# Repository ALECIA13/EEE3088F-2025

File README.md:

# EEE3088F-2025 Micro-Mouse Power Module

**Authors:** Khanyisa Hlungwani & Maitele Makungo

## Project Description

This repository contains the **Power Module** for a Micro-Mouse robot project, developed as part of the EEE3088F (2025) course. The Micromouse is a small autonomous robot designed to navigate and solve a maze, consisting of various subsystems (sensors, motors, control, and power). The Power Module handles all aspects of power distribution and management for the robot, ensuring that each component receives stable and sufficient power. It includes the circuitry for the robot’s battery power supply, voltage regulation for logic and sensors, and motor driver outputs, along with safety features like battery monitoring and charging control. Overall, this module is crucial for delivering reliable power to the Micro-Mouse, allowing it to operate safely and efficiently during maze-solving runs.

## Scope and Responsibilities

The design and implementation of the Power Module were divided between two team members, each focusing on specific functional areas:

* **Khanyisa Hlungwani:** Responsible for the **motor control** circuitry and **battery management**. This includes the motor driver hardware for the drive motors, the **battery monitoring** system to track battery voltage/health, and the **battery charging** circuit to safely recharge the robot’s Li-ion/Li-Po battery pack. Khanyisa’s design ensures the motors receive the appropriate power and that the battery is used and charged safely (with over-voltage and over-discharge protection as needed).

* **Maitele Makungo:** Responsible for the **power input interface** and **voltage regulation**. This includes the **USB-C interface** for external power/charging (allowing the robot to be powered or charged via a USB-C source), the design of **voltage regulators** (to step down or regulate battery/USB voltage to the required levels for various components such as 5V, 3.3V, etc.), and overall **power management** circuitry. Maitele’s design ensures stable regulated voltages for all electronics and handles power switching logic (for example, switching between USB power and battery, and implementing any necessary protection like current limiting or short-circuit protection).

By splitting the responsibilities, each student focused on their section of the power system while ensuring that the two parts integrate seamlessly into a single Power Module that meets the Micro-Mouse’s requirements.

## Repository Contents

The repository is organized into folders and files that represent different aspects of the Power Module design:

* **Schematics** – Contains the electrical schematics of the power module. This includes complete circuit diagrams for the battery charger/monitor, motor driver circuits, USB-C power input circuitry, and voltage regulators. The schematics are provided in the chosen EDA tool format (and may include PDF exports for easy viewing). **(e.g.,** files like `PowerModule_Schematic.pdf` and the source schematic design files **)**

* **PCB Layout** – Contains the PCB design files and layout information for the power module’s printed circuit board. This includes the board layout file from the PCB design software, as well as generated manufacturing files (Gerber files, drill files) and possibly images of the PCB layout. **(e.g.,** a board file `PowerModule_PCB.kicad_pcb` or Altium project, and exported images like `PCB_Top.png`, `PCB_Bottom.png` **)**

* **Final Design** – This folder includes the finalized documentation and outputs of the project. It typically contains the final report or design document for the power module, a Bill of Materials (BOM) listing all components used, and any presentation slides or additional references. It may also include **final revision** schematic/PCB printouts and assembly drawings, as well as test results or data from the completed module. In short, the **Final Design** folder serves as a comprehensive package of the finished power module design and can be used for review or submission purposes.

## Usage and Integration

The Power Module is designed to integrate with the Micro-Mouse robot’s overall system (often via a main control board or motherboard). Key connections and usage notes include:

* **Power Input:** The module can be powered via the on-board battery or through the USB-C port. When the Micro-Mouse is operating untethered, it draws power from the battery. When plugged into USB-C, the system can charge the battery and/or run the robot from USB power (with proper regulation and without overcharging the battery).

* **Outputs to Other Modules:** The Power Module provides regulated output lines (e.g., 5V, 3.3V) that connect to the Micro-Mouse’s other subsystems (like the sensor module and control electronics) via a designated connector. It also provides the motor driver outputs that connect directly to the motors on the chassis. These interface connections are clearly labeled in the schematic and on the PCB silkscreen for easy assembly.

* **Battery Monitoring:** The on-board battery voltage sensor can be read by the main controller (or a dedicated microcontroller on the power board) to determine the battery charge level. This allows the robot’s software to warn about low battery or manage charging states. Users should ensure the battery is within safe voltage ranges during operation (the module includes under-voltage lockout to protect the battery).

* **Charging:** To charge the robot, connect a USB-C cable to the Power Module’s port. The charging circuit will automatically manage the charging current and cutoff based on the battery’s state. Indicator LEDs (if included on the PCB) may show the charging status (charging, full, etc.). It’s recommended to refer to the **Final Design** document for specifics on the charging procedure and any jumpers or switches related to power sourcing.

## Getting Started

To get started with this Power Module repository:

1. **Clone the Repository:** Download or clone the repo to access all design files. Ensure you have the necessary software to open the schematic (`Schematics` folder) and PCB layout files (`PCB Layout` folder). For example, if the design was done in KiCad, download KiCad to open the project; if Altium, use Altium Designer, etc.

2. **Open the Schematic:** Review the power module schematic to understand the circuit design. This can be found in the **Schematics** folder (use the PDF for a quick view, or the source file for editing). The schematic is annotated with comments to explain the role of each section (battery charger, motor driver, etc.).

3. **Examine the PCB Layout:** Open the PCB design in the appropriate software to see component placement and routing. Alternatively, view the provided PCB images in the **PCB Layout** folder to get an overview of the board’s design (component locations, board dimensions, connectors, etc.).

4. **Read the Documentation:** In the **Final Design** folder, read the final report or documentation which includes detailed descriptions of design decisions, testing procedures, and results. This will provide insight into why certain components were chosen and how the module was verified to meet requirements.

5. **Integration:** If you are integrating this Power Module with your own Micro-Mouse project, use the interfacing information (pinouts and diagrams) provided in the documentation to connect the module properly. The **Micro-Mouse System Interfacing** section of the report (in **Final Design**) describes how this power board connects to the main controller board and motors.

## Contributing

This project was completed as an academic course project by the authors, so it may not be open for external contributions in the usual sense. However, if you are an instructor or student looking to use this design as a reference or extend it:

* Feel free to fork the repository for your own educational use.
* If you find issues or have suggestions, you can contact the authors or open an issue for discussion.
* Ensure to credit the original authors (Khanyisa Hlungwani and Maitele Makungo) if you derive or use significant portions of this design in your own project.

## Acknowledgments

* **Course Instructors and Mentors:** Thank you to the EEE3088F course instructors for guidance throughout the project, and for providing the framework and resources for the Micro-Mouse competition project.
* **Teammates:** Appreciation to each other as team members for the collaboration and division of work that made this Power Module successful.
* **Resources:** The Micro-Mouse community and prior projects provided inspiration and insight. Resources like online Micromouse forums and documentation helped shape the design (for example, understanding common voltage requirements and battery choices for micromouse robots).

---

*This README provides an overview of the Power Module for the EEE3088F-2025 Micro-Mouse project. For detailed schematics, PCB layouts, and test results, please refer to the files and documentation within this repository. We hope this information is helpful for anyone studying or building a Micro-Mouse power system.*

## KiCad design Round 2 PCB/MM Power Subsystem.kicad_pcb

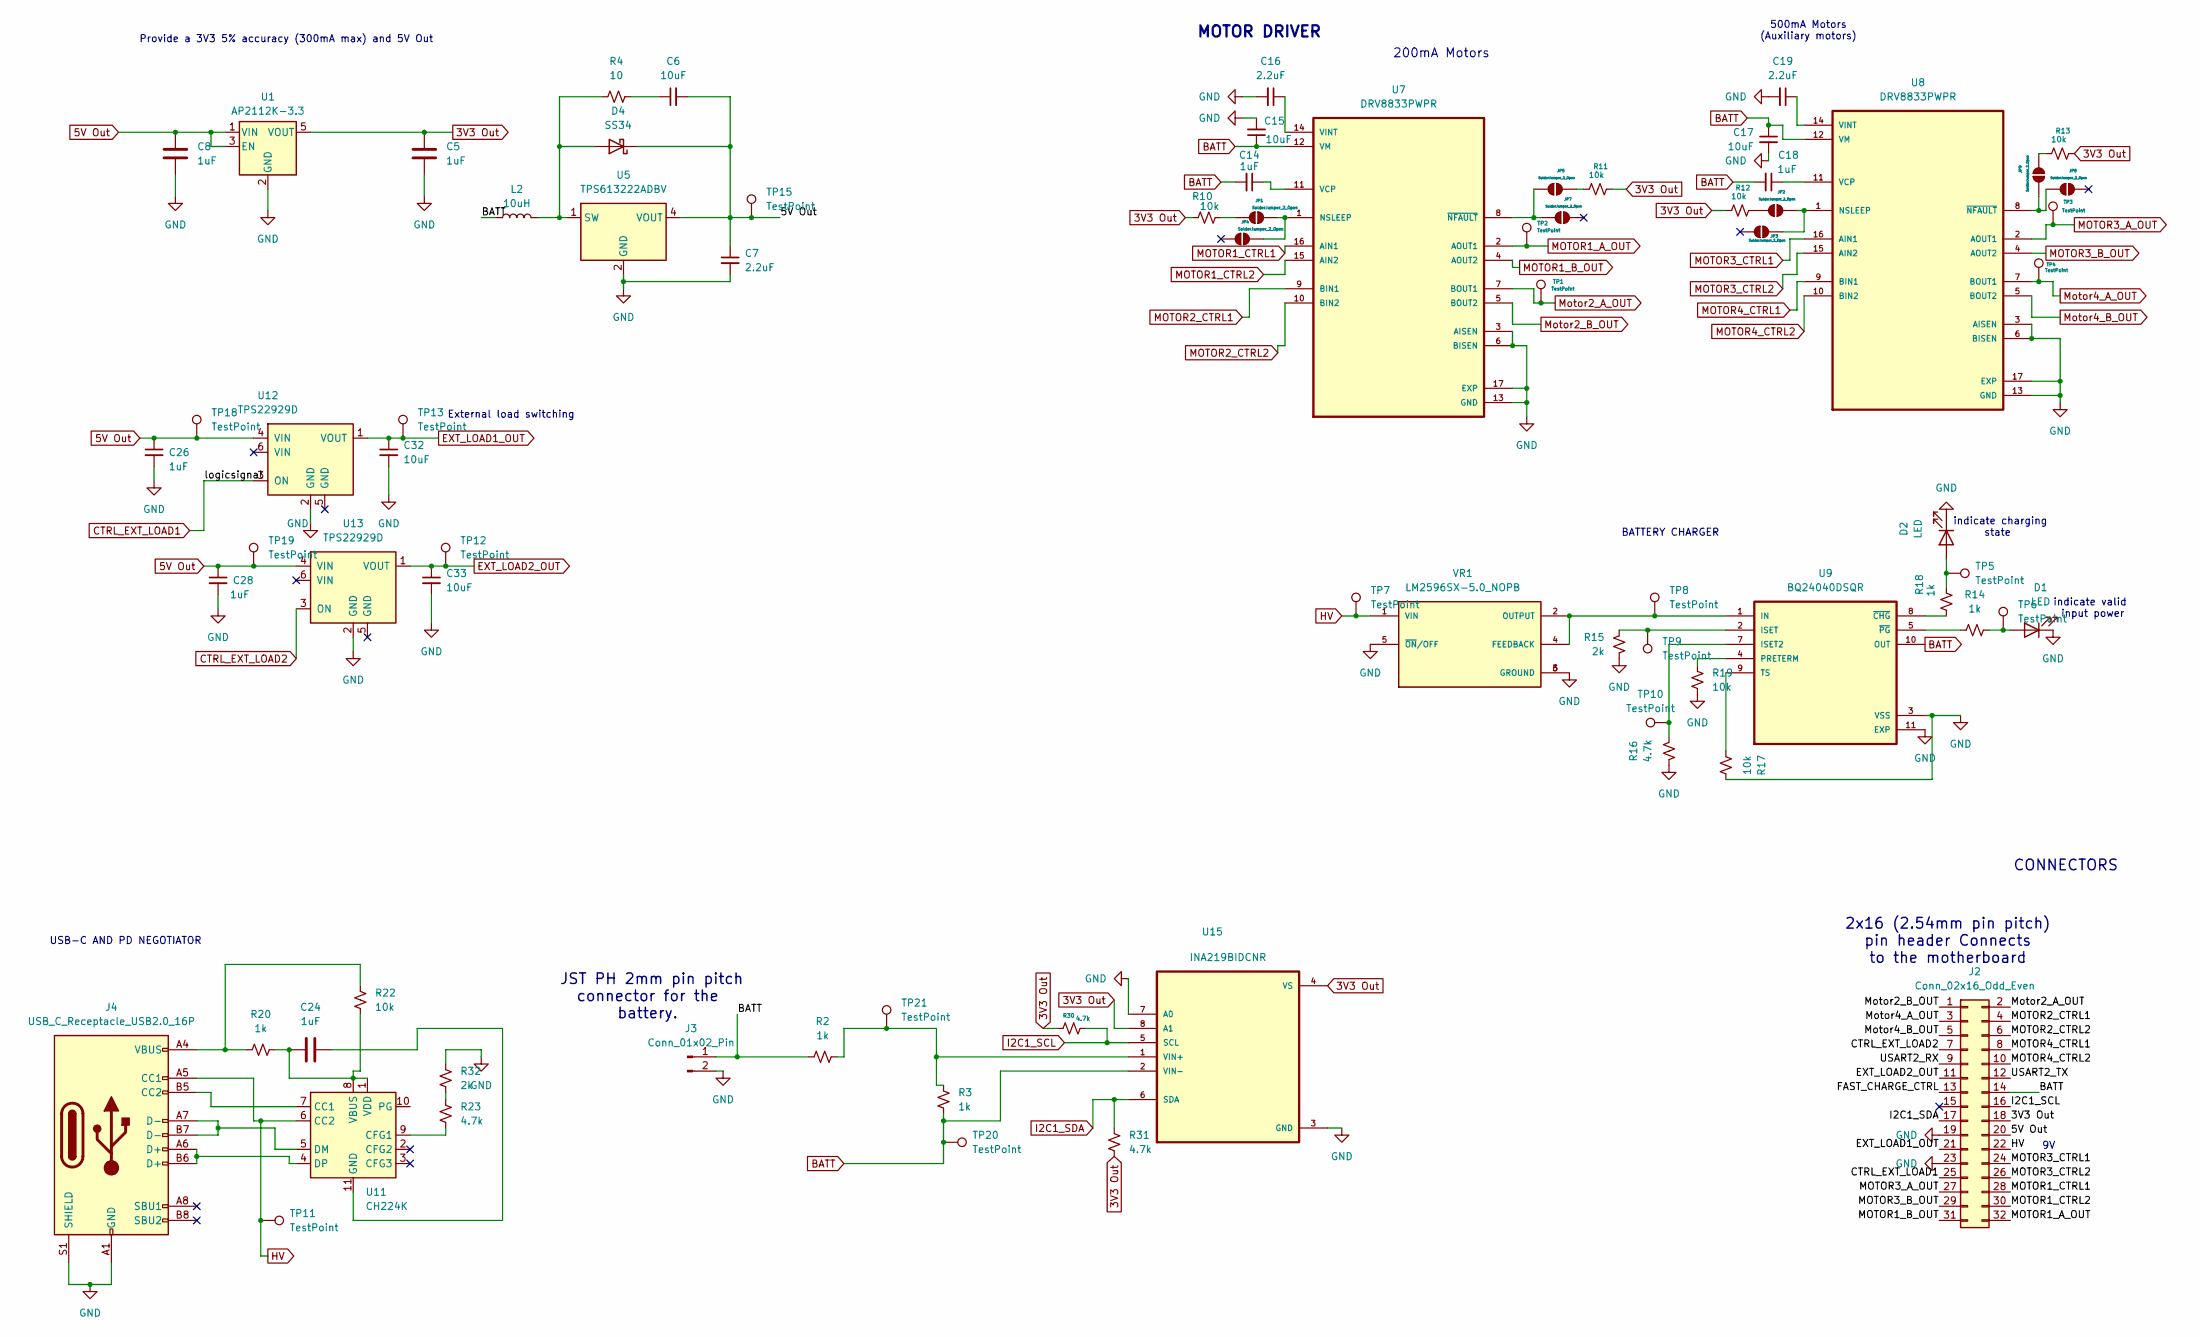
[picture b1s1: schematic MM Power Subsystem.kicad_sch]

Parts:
C5, C8, C14, C18, C24, C26, C28: 1uF; C_0402_1005Metric_Pad0.74x0.62mm_HandSolder
C6, C15, C17, C32, C33: 10uF; C_0402_1005Metric_Pad0.74x0.62mm_HandSolder
C7, C16, C19: 2.2uF; C_0402_1005Metric_Pad0.74x0.62mm_HandSolder
D1, D2: LED; LED_0805_2012Metric_Pad1.15x1.40mm_HandSolder
D4: SS34; D_SMA
J2: Conn_02x16_Odd_Even; PinHeader_2x16_P2.54mm_Vertical
J3: Conn_01x02_Pin; JST_PH_S2B-PH-K_1x02_P2.00mm_Horizontal
J4: USB_C_Receptacle_USB2.0_16P; USB_C_Receptacle_HCTL_HC-TYPE-C-16P-01A; LCSC C134092
JP1, JP2, JP3, JP4, JP5, JP7, JP8, JP9: SolderJumper_2_Open; SolderJumper-2_P1.3mm_Open_RoundedPad1.0x1.5mm
L2: 10uH; L_0201_0603Metric_Pad0.64x0.40mm_HandSolder
R2, R3, R14, R18, R20: 1k; R_0402_1005Metric_Pad0.72x0.64mm_HandSolder
R4: 10; R_0402_1005Metric_Pad0.72x0.64mm_HandSolder
R10, R11, R12, R13, R17, R19, R22: 10k; R_0402_1005Metric_Pad0.72x0.64mm_HandSolder
R15, R32: 2k; R_0402_1005Metric_Pad0.72x0.64mm_HandSolder
R16, R23, R30, R31: 4.7k; R_0402_1005Metric_Pad0.72x0.64mm_HandSolder
TP1, TP2, TP3, TP4, TP5, TP6, TP7, TP8, TP9, TP10, TP11, TP12, TP13, TP15, TP18, TP19, TP20, TP21: TestPoint; TestPoint_Pad_D2.0mm
U1: AP2112K-3.3; SOT-23-5
U5: TPS613222ADBV; SOT-23-5; LCSC C2071163
U7, U8: DRV8833PWPR; TSSOP-16-1EP_4.4x5mm_P0.65mm_EP3x3mm; PARTREV E; LCSC C50506
U9: BQ24040DSQR; WSON-10-1EP_2.5x2.5mm_P0.5mm_EP1.2x2mm; LCSC C81080
U11: CH224K; SSOP-10-1EP_3.9x4.9mm_P1mm_EP2.1x3.3mm
U12, U13: TPS22929D; SOT-23-6; LCSC C415177
U15: INA219BIDCNR; SOT65P280X145-8N
VR1: LM2596SX-5.0_NOPB; VREG_LM2596SX-5.0_NOPB; PARTREV F; LCSC C10002

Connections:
3V3 Out: C5.1, J2.18, R10.2, R11.1, R12.2, R13.1, R30.2, R31.2, U1.5 (VOUT), U15.4 (VS), U15.8 (A1)
5V Out: C6.2, C7.1, C8.1, C26.1, C28.1, D4.1 (K), J2.20, TP15.1, TP18.1, TP19.1, U1.1 (VIN), U1.3 (EN), U5.4 (VOUT), U12.4 (VIN), U13.4 (VIN)
/FAST_CHARGE_CTRL: J2.13
/MOTOR1_A_OUT: J2.32
/MOTOR1_CTRL1: J2.28
/MOTOR1_CTRL2: J2.30
/MOTOR2_CTRL1: J2.4
/MOTOR2_CTRL2: J2.6
/MOTOR3_A_OUT: J2.27
/MOTOR3_B_OUT: J2.29
/MOTOR3_CTRL1: J2.24
/MOTOR4_CTRL1: J2.8
/Motor2_B_OUT: J2.1
/Motor4_B_OUT: J2.5
/USART2_RX: J2.9
/USART2_TX: J2.12
BATT: C14.2, C15.1, C17.1, C18.2, J2.14, J3.1, L2.1, R2.2, R3.2, TP20.1, U7.12 (VM), U8.12 (VM), U9.10 (OUT), U15.2 (VIN-)
CTRL_EXT_LOAD1: J2.25, U12.3 (ON)
CTRL_EXT_LOAD2: J2.7, U13.3 (ON)
EXT_LOAD1_OUT: C32.1, J2.21, TP13.1, U12.1 (VOUT)
EXT_LOAD2_OUT: C33.1, J2.11, TP12.1, U13.1 (VOUT)
GND: C5.2, C7.2, C8.2, C15.2, C16.2, C17.2, C19.2, C26.2, C28.2, C32.2, C33.2, D1.1 (K), D2.1 (K), J2.19, J2.23, J3.2, J4.A1 (GND), J4.A12 (GND), J4.B1 (GND), J4.B12 (GND), J4.S1 (SHIELD), R15.1, R16.1, R17.1, R19.2, R32.1, U1.2 (GND), U5.2 (GND), U7.3 (AISEN), U7.6 (BISEN), U7.13 (GND), U7.17 (EXP), U8.3 (AISEN), U8.6 (BISEN), U8.13 (GND), U8.17 (EXP), U9.3 (VSS), U9.11 (EXP), U12.2 (GND), U13.2 (GND), U15.3 (GND), U15.7 (A0), VR1.3 (GROUND), VR1.5 (~ON/OFF), VR1.6 (GROUND)
HV: J2.22, J4.A5 (CC1), TP7.1, TP11.1, U11.6 (CC2), VR1.1 (VIN)
I2C1_SCL: J2.16, R30.1, U15.5 (SCL)
I2C1_SDA: J2.17, R31.1, U15.6 (SDA)
MOTOR1_A_OUT: TP2.1, U7.2 (AOUT1)
MOTOR1_B_OUT: J2.31, U7.4 (AOUT2)
MOTOR1_CTRL1: U7.16 (AIN1)
MOTOR1_CTRL2: U7.15 (AIN2)
MOTOR2_CTRL1: U7.9 (BIN1)
MOTOR2_CTRL2: U7.10 (BIN2)
MOTOR3_A_OUT: TP3.1, U8.2 (AOUT1)
MOTOR3_B_OUT: U8.4 (AOUT2)
MOTOR3_CTRL1: U8.16 (AIN1)
MOTOR3_CTRL2: J2.26, U8.15 (AIN2)
MOTOR4_CTRL1: U8.9 (BIN1)
MOTOR4_CTRL2: J2.10, U8.10 (BIN2)
Motor2_A_OUT: J2.2, TP1.1, U7.7 (BOUT1)
Motor2_B_OUT: U7.5 (BOUT2)
Motor4_A_OUT: J2.3, TP4.1, U8.7 (BOUT1)
Motor4_B_OUT: U8.5 (BOUT2)
unnamed: C6.1, R4.1
unnamed: D1.2 (A), R14.1, TP6.1
unnamed: D2.2 (A), R18.1, TP5.1
unnamed: D4.2 (A), L2.2, R4.2, U5.1 (SW)
unnamed: J4.B5 (CC2), U11.7 (CC1)
unnamed: J4.A4 (VBUS), J4.A9 (VBUS), J4.B4 (VBUS), J4.B9 (VBUS), R20.1, R22.1
unnamed: JP1.1 (A), R10.1
unnamed: JP1.2 (B), JP4.2 (B), U7.1 (NSLEEP)
unnamed: JP2.1 (A), R12.1
unnamed: JP2.2 (B), JP3.2 (B), U8.1 (NSLEEP)
unnamed: JP5.1 (A), JP7.1 (A), U7.8 (~NFAULT)
unnamed: JP5.2 (B), R11.2
unnamed: JP8.1 (A), JP9.1 (A), U8.8 (~NFAULT)
unnamed: JP9.2 (B), R13.2
unnamed: R23.1, R32.2
unnamed: C14.1, U7.11 (VCP)
unnamed: C16.1, U7.14 (VINT)
unnamed: C18.1, U8.11 (VCP)
unnamed: C19.1, U8.14 (VINT)
unnamed: TP8.1, U9.1 (IN), VR1.2 (OUTPUT), VR1.4 (FEEDBACK)
unnamed: R16.2, TP10.1, U9.7 (ISET2)
unnamed: R15.2, TP9.1, U9.2 (ISET)
unnamed: R19.1, U9.4 (PRETERM)
unnamed: R17.2, U9.9 (TS)
unnamed: R18.2, U9.8 (~CHG)
unnamed: R14.2, U9.5 (~PG)
unnamed: R23.2, U11.9 (CFG1)
unnamed: J4.A7 (D-), J4.B7 (D-), U11.5 (DM)
unnamed: J4.A6 (D+), J4.B6 (D+), U11.4 (DP)
unnamed: C24.2, U11.11 (GND)
unnamed: C24.1, R20.2, R22.2, U11.1 (VDD), U11.8 (VBUS)
unnamed: R2.1, R3.1, TP21.1, U15.1 (VIN+)

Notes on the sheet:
Provide a 3V3 5% accuracy (300mA max) and 5V Out
BATTERY CHARGER
JST PH 2mm pin pitch connector for the battery.
External load switching
indicate charging state
500mA Motors (Auxiliary motors)
MOTOR DRIVER
indicate valid input power
2x16 (2.54mm pin pitch) pin header Connects to the motherboard
CONNECTORS
USB-C AND PD NEGOTIATOR
200mA Motors

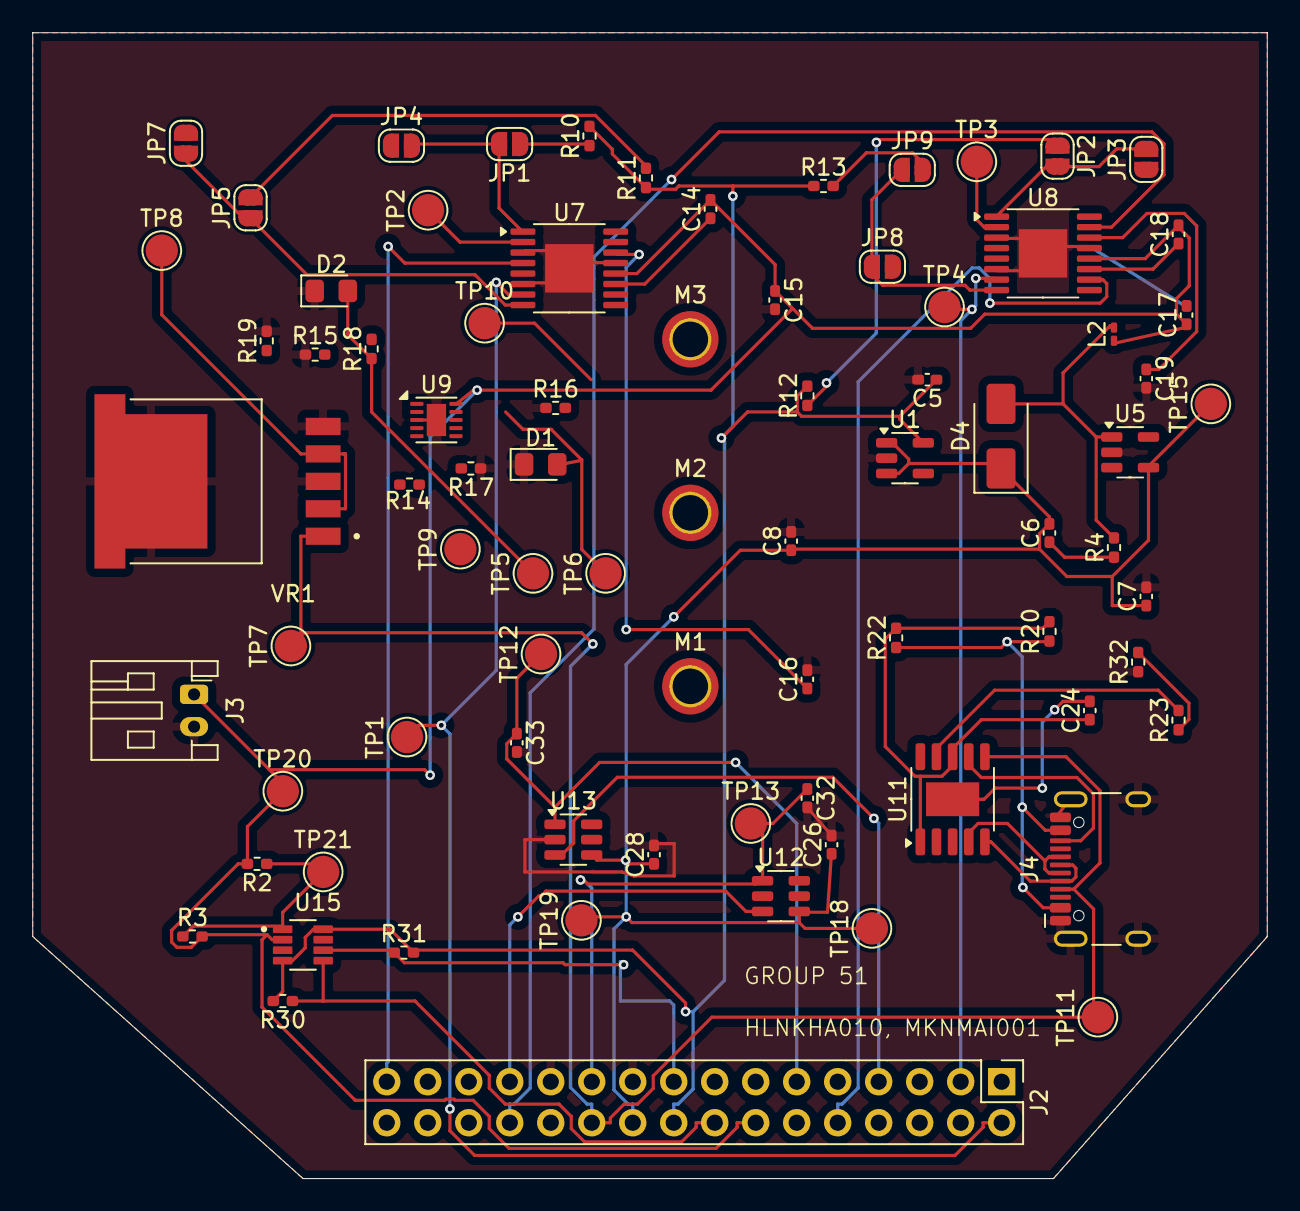
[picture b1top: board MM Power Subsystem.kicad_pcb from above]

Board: 2 copper layers, 76.5 x 71.0 mm, 80 parts (0 on the bottom side), 50 nets.

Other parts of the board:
M1, M2, M3: MountingHole_2.2mm_M2_ISO7380_Pad_TopBottom

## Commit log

2025-03-08 Update README.md
    Added design decisions
2025-03-17 Update README.md
    Updated workload breakdown
2025-03-17 Update README.md
    added the names of the authors
2025-03-17 Create Datasheets
    added a datasheets file
2025-03-17 Add files via upload
    uploaded motor driver datasheet
2025-03-19 Create Motor driver datasheet_drv8833
2025-03-19 Create Motor drive
2025-03-19 Add files via upload
    motor driver datasheet
2025-03-19 Add files via upload
    motor driver(2nd option) but this is for DC/Stepper Motor
2025-03-19 Add files via upload
    Added the TB6612FNG motor driver datasheet(This is most likely to be the motor driver that will be used)
2025-03-22 Add files via upload
    battery charger IC
2025-03-26 kicadschematics
2025-03-26 Create Power design
    full circuit
2025-03-27 Create Power
    final design
2025-03-27 Add files via upload
    FINAL DESIGN
2025-03-28 Create proj
2025-04-09 Create Design
2025-04-09 Add files via upload
    added files for second submission
2025-04-12 Update README.md
    Project define
2025-04-25 Update README.md
    edited readme file
